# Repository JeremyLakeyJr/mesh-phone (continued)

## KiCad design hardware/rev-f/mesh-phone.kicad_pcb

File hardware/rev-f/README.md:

# Owasso1 Rev F — engineering checkpoint, not a fabrication release

Open `mesh-phone.kicad_pro` in this directory. The project in `../main/` is
the preserved original, not this corrected revision.

Implemented in schematic and PCB:

- MAX-M10S GPS with passive-antenna U.FL, UART, PPS and bypass capacitors.
- Rear keyed 10-pin JST-GH expansion interface, with a current-limited 3.3 V
  supply and shared SPI/I²C. Switch off and disconnect USB before swapping.
- MCU EN/BOOT support, usable SPI pin assignments, keypad expander pin-order
  corrections, display controls and I²C pull-ups.
- Removal of the switch connection that directly joined USB 5 V to the battery.
- Reconciled schematic/PCB pad contracts, with original component placements
  preserved. New parts are rear-mounted.

Read [INTERFACES.md](INTERFACES.md) before designing a module. This is a keyed
cable connector, not a finished blind-mate mechanical docking system.

## Not safe to order or power yet

The inherited battery protection, charger/power path, 3.3 V regulator and 5 V
boost circuits still require redesign. The A7670E modem/carrier is not approved
for the US target. Remaining radio-control, IR, fuel-gauge, RFID and SIM
interfaces are incomplete. See the full
[connection review](../../docs/reviews/review-2026-09-20/CONNECTION_REVIEW.md).

RF/USB impedance and antenna/enclosure placement are unverified. Ground vias
at the new reset circuitry overlap solderable pads; move them outside pads or
specify a suitable filled/capped via process during the final DFM pass. Do not
assume ordinary open vias in solder pads are assembly-ready.

## Verification evidence

Latest checkpoint: **608/608 contract and placement checks passed**. Native
KiCad DRC reports **0 errors, 0 unconnected items and 0 schematic-parity
findings**, with 5 footprint-library mismatch warnings. ERC still reports
**2 errors and 24 warnings** from unresolved supply modelling and interfaces.
The five footprint warnings concern J10, USB1, U1, J14 and J3; their modified
pad/geometry contracts need final library and manufacturer-drawing review.

- `verification-summary.json`: independent net/placement checks, native tool
  counts and SHA-256 fingerprints of the checked files.
- `drc-final.json`: native KiCad DRC, including schematic parity.
- `erc.json`: unresolved electrical-rule findings, not waived with power flags.
- `owasso1-engineering.pdf`: two-sheet schematic for review.
- `previews/`: schematic SVGs.

Zero routing errors would not certify circuit operation. Firmware, bench
bring-up, battery-safety verification, RF tests and cellular carrier acceptance
are still required. No revised manufacturing package has been released.

To repeat the read-only contract checks, run `python scripts/verify_revF.py` from the
repository root after exporting a fresh `netlist.xml`. The build/routing and
layout experiment scripts in `../../archive/scripts/` are checkpoint tools, not an
idempotent pipeline: do not replay them on this finished checkpoint.

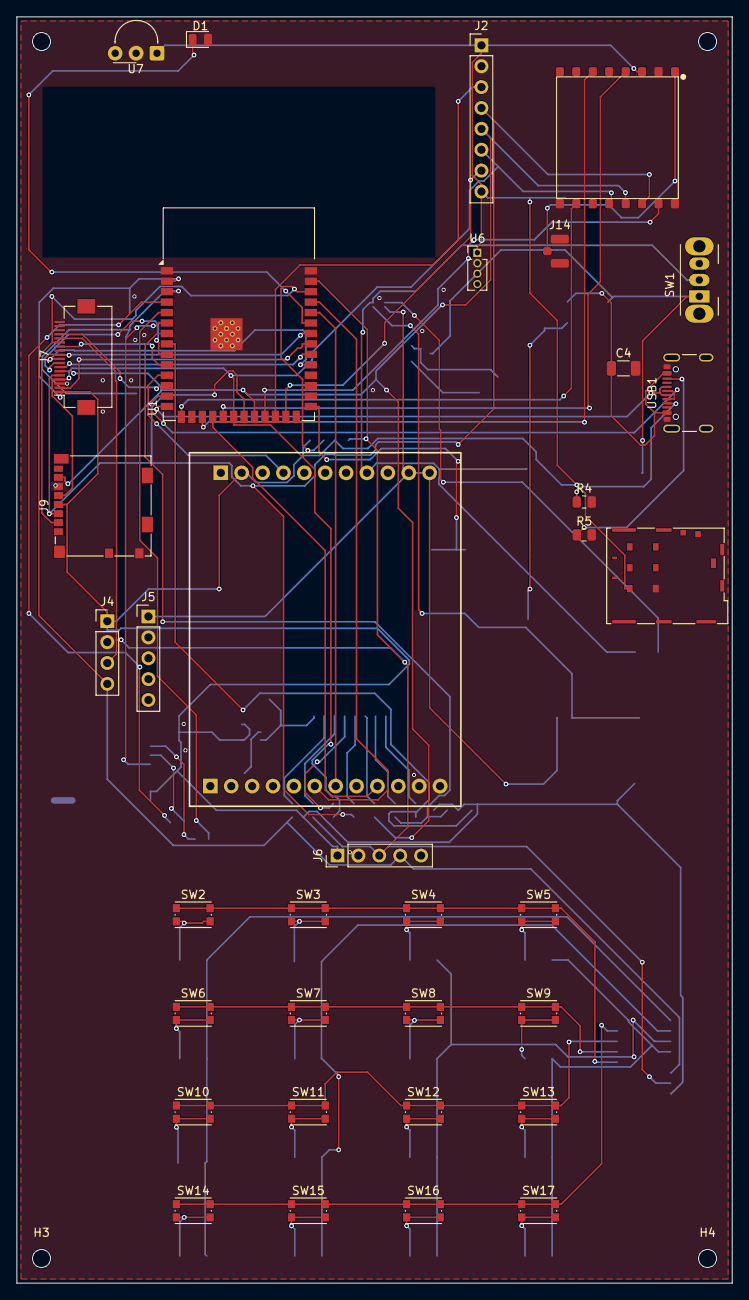
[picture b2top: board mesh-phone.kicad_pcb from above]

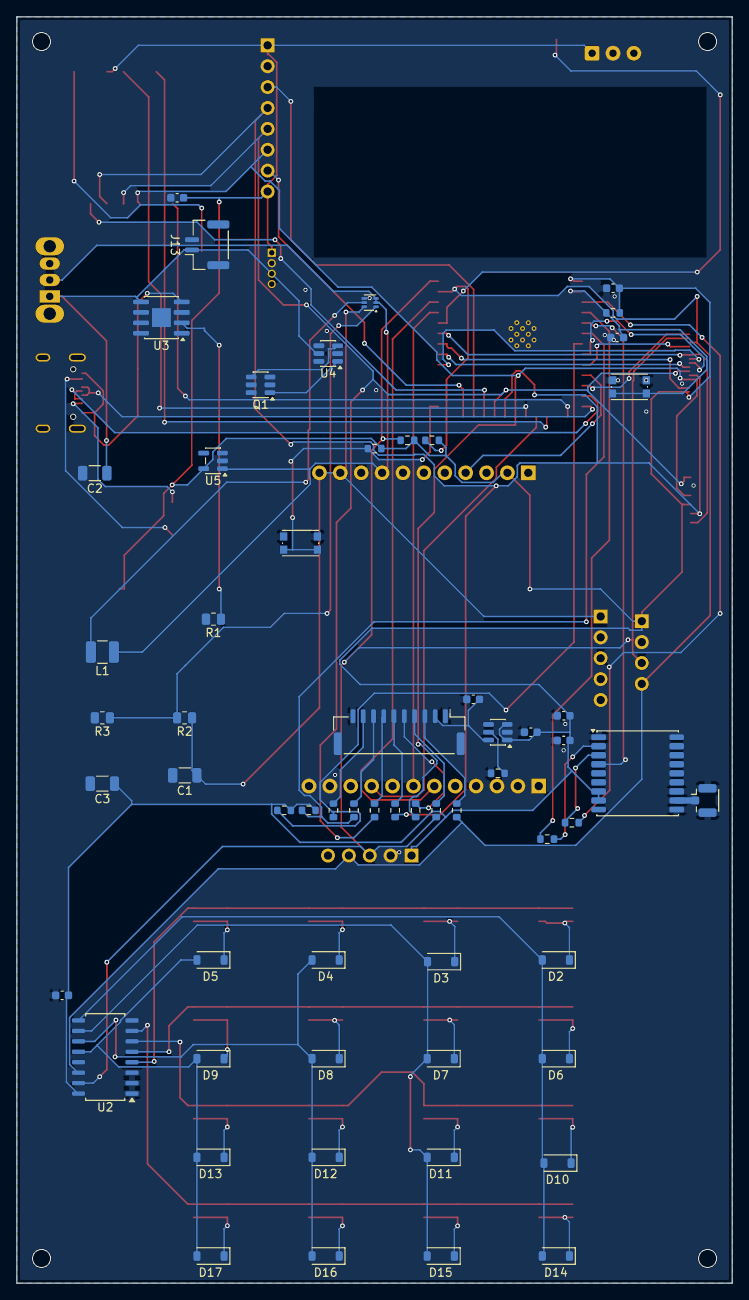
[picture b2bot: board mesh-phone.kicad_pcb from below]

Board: 2 copper layers, 87.0 x 154.0 mm, 99 parts (61 on the bottom side), 82 nets.

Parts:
C1: 1000uF-MODEM-BULK; C_1206_3216Metric
C2: 100uF-VBAT-BULK; C_1206_3216Metric
C3: 10uF-3V3-BULK; C_1206_3216Metric
C4: 10uF-USB-IN; C_1206_3216Metric
C5, C9: 10uF 10V X5R; C_0603_1608Metric
C6, C10, C11, C12: 100nF 10V X7R; C_0603_1608Metric
C7, C8: 1uF 10V X7R; C_0603_1608Metric
D1: TSAL6200-IR-LED; LED_0805_2012Metric
D2: 1N4148W-KEY-1; D_SOD-123
D3: 1N4148W-KEY-2; D_SOD-123
D4: 1N4148W-KEY-3; D_SOD-123
D5: 1N4148W-KEY-4; D_SOD-123
D6: 1N4148W-KEY-5; D_SOD-123
D7: 1N4148W-KEY-6; D_SOD-123
D8: 1N4148W-KEY-7; D_SOD-123
D9: 1N4148W-KEY-8; D_SOD-123
D10: 1N4148W-KEY-9; D_SOD-123
D11: 1N4148W-KEY-10; D_SOD-123
D12: 1N4148W-KEY-11; D_SOD-123
D13: 1N4148W-KEY-12; D_SOD-123
D14: 1N4148W-KEY-13; D_SOD-123
D15: 1N4148W-KEY-14; D_SOD-123
D16: 1N4148W-KEY-15; D_SOD-123
D17: 1N4148W-KEY-16; D_SOD-123
H1, H2, H3, H4: MountingHole_2.2mm_M2
J1: A7670E-LASE-23P-12+11; A7670E_LASE_23P_12+11
J2: CC1101-module; PinHeader_1x08_P2.54mm_Vertical
J3: Ra-01SH-SX1262-915MHz; Ra-01SH
J4: PN532-NFC-module; PinHeader_1x04_P2.54mm_Vertical
J5: RDM6300-RFID-module; PinHeader_1x05_P2.54mm_Vertical
J6: Pimoroni-PIM447-Trackball; PinHeader_1x05_P2.54mm_Vertical
J7: Waveshare-3.5in-18pin-FPC; Hirose_FH12-18S-0.5SH_1x18-1MP_P0.50mm_Horizontal
J9: MicroSD-SPI; microSD_HC_Molex_104031-0811
J10: Nano-SIM; JAE_SIM_Card_SF72S006
J13: LiPo-BATTERY-MICRO-JST-1.25; JST_GH_SM02B-GHS-TB_1x02-1MP_P1.25mm_Horizontal
J14: LoRa-UFL-Antenna; U.FL_Hirose_U.FL-R-SMT-1_Vertical
J15: GPS PASSIVE ANTENNA; U.FL_Hirose_U.FL-R-SMT-1_Vertical
J16: REAR EXPANSION - POWER OFF TO SWAP; JST_GH_BM10B-GHS-TBT_1x10-1MP_P1.25mm_Vertical
L1: 1uH-BOOST-INDUCTOR; L_1210_3225Metric
Q1: FS8205A-PROTECTION-FET; SOT-23-6
R1: 1.2k-TP4056-PROG; R_0805_2012Metric
R2: 180k-BOOST-FB; R_0805_2012Metric
R3: 27k-BOOST-FB; R_0805_2012Metric
R4: 5.1k-USB-C-CC1-Rd; R_0805_2012Metric
R5: 5.1k-USB-C-CC2-Rd; R_0805_2012Metric
R6, R7: 1k; R_0603_1608Metric
R8, R9, R12, R13: 10k; R_0603_1608Metric
R10, R11: 4.7k; R_0603_1608Metric
R14: 232k 1%; R_0603_1608Metric
R15, R16, R17, R18, R19, R20, R21: 33; R_0603_1608Metric
SW1: Power-switch; SW_Slide_SPDT_Angled_CK_OS102011MA1Q
SW2: KEY-1; SW_Push_1P1T_NO_CK_KMR2
SW3: KEY-2; SW_Push_1P1T_NO_CK_KMR2
SW4: KEY-3; SW_Push_1P1T_NO_CK_KMR2
SW5: KEY-4; SW_Push_1P1T_NO_CK_KMR2
SW6: KEY-5; SW_Push_1P1T_NO_CK_KMR2
SW7: KEY-6; SW_Push_1P1T_NO_CK_KMR2
SW8: KEY-7; SW_Push_1P1T_NO_CK_KMR2
SW9: KEY-8; SW_Push_1P1T_NO_CK_KMR2
SW10: KEY-9; SW_Push_1P1T_NO_CK_KMR2
SW11: KEY-10; SW_Push_1P1T_NO_CK_KMR2
SW12: KEY-11; SW_Push_1P1T_NO_CK_KMR2
SW13: KEY-12; SW_Push_1P1T_NO_CK_KMR2
SW14: KEY-13; SW_Push_1P1T_NO_CK_KMR2
SW15: KEY-14; SW_Push_1P1T_NO_CK_KMR2
SW16: KEY-15; SW_Push_1P1T_NO_CK_KMR2
SW17: KEY-16; SW_Push_1P1T_NO_CK_KMR2
SW18: BOOT; SW_Push_1P1T_NO_CK_KMR2
SW19: RESET; SW_Push_1P1T_NO_CK_KMR2
U1: ESP32-S3-WROOM-1-N16R8; ESP32-S3-WROOM-1
U2: PCF8574T-keypad-expander; SOIC-16_4.55x10.3mm_P1.27mm
U3: TP4056-charger; HSOP-8-1EP_3.9x4.9mm_P1.27mm_EP2.3x2.3mm
U4: DW01A-protection; SOT-23-6
U5: 3V3-LDO; SOT-23-5
U6: MAX17048-fuel-gauge; PinHeader_1x04_P1.27mm_Vertical
U7: TSOP38238-IR-receiver; Vishay_MINIMOLD-3Pin
U8: TPS61023DRLR-5V-BOOST; SOT-563
U9: MAX-M10S-00B-01; ublox_MAX
U10: TPS2553DBVR; SOT-23-6
USB1: USB-C-charge-and-data; USB_C_Receptacle_GCT_USB4105-xx-A_16P_TopMnt_Horizontal

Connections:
/3V3: C3.1, C5.1, C6.1, C8.1, C10.1, C11.1, C12.1, J1.14, J2.1, J2.8, J3.3, J4.1, J6.1, J7.1, J9.4, J10.1, R8.1, R9.1, R10.1, R11.1, R12.1, R13.1, U1.2, U2.16, U5.5, U6.1, U7.1, U9.7, U9.8, U10.1, U10.3
/BAT_CHARGE: C2.1, J13.1, SW1.1, U3.5, U4.5, U6.3
/BOOST_FB: R2.2, R3.1, U8.1
/BOOST_SW: L1.2, U8.5
/CC1101_CS: J2.3, U1.24
/CC1101_GDO0: J2.7, U1.25
/DW01A_OC: Q1.4, U4.3
/DW01A_OD: Q1.1, U4.1
/EXP_CS: R12.2, R20.1, U1.7
/EXP_IRQ: R13.2, R21.1, U1.8
/GND: C1.2, C2.2, C3.2, C4.2, C5.2, C6.2, C7.2, C8.2, C9.2, C10.2, C11.2, C12.2, D1.2, J1.11, J1.12, J2.2, J3.2, J3.9, J3.16, J4.2, J5.2, J6.2, J7.3, J9.6, J9.10, J10.2, J13.2, J14.2, J15.2, J16.1, J16.10, Q1.2, Q1.3, Q1.5, Q1.6, R1.2, R3.2, R4.2, R5.2, R14.2, SW18.2, SW19.2, U1.1, U1.40, U1.41, U2.1, U2.2, U2.3, U2.8, U3.3, U3.9, U4.2, U4.4, U4.6, U5.2, U6.2, U7.2, U8.4, U9.1, U9.10, U9.12, U10.2, USB1.1, USB1.12, USB1.13, USB1.22
/GPS and rear expansion/EXP_3V3: C9.1, J16.2, U10.6
/GPS and rear expansion/EXP_CS_PORT: J16.8, R20.2
/GPS and rear expansion/EXP_ILIM: R14.1, U10.5
/GPS and rear expansion/EXP_IRQ_PORT: J16.9, R21.2
/GPS and rear expansion/EXP_MISO: J16.7, R19.2
/GPS and rear expansion/EXP_MOSI: J16.6, R18.2
/GPS and rear expansion/EXP_SCK: J16.5, R17.2
/GPS and rear expansion/EXP_SCL: J16.3, R15.2
/GPS and rear expansion/EXP_SDA: J16.4, R16.2
/GPS and rear expansion/GPS_ANT: J15.1, U9.11
/GPS and rear expansion/GPS_RX: R6.2, U9.3
/GPS and rear expansion/GPS_TX: R7.1, U9.2
/GPS_HOST_RX: R7.2, U1.5
/GPS_HOST_TX: R6.1, U1.4
/GPS_PPS: U1.6, U9.4
/I2C_SCL: J4.4, J6.4, J7.13, R10.2, R15.1, U1.38, U2.14
/I2C_SDA: J4.3, J6.3, J7.14, R11.2, R16.1, U1.39, U2.15
/IR_TX: D1.1, U1.35
/KEY_C1: D2.2, D6.2, D10.2, D14.2, U2.9
/KEY_C2: D3.2, D7.2, D11.2, D15.2, U2.10
/KEY_C3: D4.2, D8.2, D12.2, D16.2, U2.11
/KEY_C4: D5.2, D9.2, D13.2, D17.2, U2.12
/KEY_D1: D2.1, SW2.2
/KEY_D2: D3.1, SW3.2
/KEY_D3: D4.1, SW4.2
/KEY_D4: D5.1, SW5.2
/KEY_D5: D6.1, SW6.2
/KEY_D6: D7.1, SW7.2
/KEY_D7: D8.1, SW8.2
/KEY_D8: D9.1, SW9.2
/KEY_D9: D10.1, SW10.2
/KEY_D10: D11.1, SW11.2
/KEY_D11: D12.1, SW12.2
/KEY_D12: D13.1, SW13.2
/KEY_D13: D14.1, SW14.2
/KEY_D14: D15.1, SW15.2
/KEY_D15: D16.1, SW16.2
/KEY_D16: D17.1, SW17.2
/KEY_R1: SW2.1, SW3.1, SW4.1, SW5.1, U2.4
/KEY_R2: SW6.1, SW7.1, SW8.1, SW9.1, U2.5
/KEY_R3: SW10.1, SW11.1, SW12.1, SW13.1, U2.6
/KEY_R4: SW14.1, SW15.1, SW16.1, SW17.1, U2.7
/LCD_BL: J7.2, U1.33
/LCD_CS: J7.9, U1.31
/LCD_DC: J7.7, U1.32
/LCD_RESET: J7.8, U1.9
/LORA_ANT: J3.1, J14.1
/LTE_PWRKEY: J1.9, U1.18
/LTE_RI: J1.16, U1.11
/LTE_RX: J1.7, U1.36
/LTE_TX: J1.6, U1.37
/MCU_BOOT: R9.2, SW18.1, U1.27
/MCU_EN: C7.1, R8.2, SW19.1, U1.3
/MODEM_5V: C1.1, J1.22, J1.23, J5.1, R2.1, U8.6
/SD_CS: J7.10, J9.2, U1.34
/SPI_MISO: J2.5, J3.13, J7.6, J9.7, R19.1, U1.22
/SPI_MOSI: J2.4, J3.14, J7.5, J9.3, R18.1, U1.21
/SPI_SCK: J2.6, J3.12, J7.4, J9.5, R17.1, U1.20
/SX1262_BUSY: J3.10, U1.15
/SX1262_CS: J3.15, U1.23
/SX1262_DIO1: J3.6, U1.17
/SX1262_RESET: J3.4, U1.19
/TOUCH_INT: J7.15, U1.12
/TP_RESET: J7.12, U1.10
/U3_PROG: R1.1, U3.2
/USB_CC1: R4.1, USB1.5
/USB_CC2: R5.1, USB1.15
/USB_D+: U1.14, USB1.6, USB1.16
/USB_D-: U1.13, USB1.7, USB1.17
/VBAT: J1.20, L1.1, SW1.2, U5.1, U8.2, U8.3
/VBUS5V: C4.1, U3.4, USB1.4, USB1.9, USB1.14, USB1.19

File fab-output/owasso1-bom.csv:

"Refs","Value","Footprint","Qty","DNP"
"C1","1000uF-MODEM-BULK","Capacitor_SMD:C_1206_3216Metric","1",""
"C2","100uF-VBAT-BULK","Capacitor_SMD:C_1206_3216Metric","1",""
"C3","10uF-3V3-BULK","Capacitor_SMD:C_1206_3216Metric","1",""
"C4","10uF-USB-IN","Capacitor_SMD:C_1206_3216Metric","1",""
"D1","TSAL6200-IR-LED","LED_SMD:LED_0805_2012Metric","1",""
"D2","1N4148W-KEY-1","Diode_SMD:D_SOD-123","1",""
"D3","1N4148W-KEY-2","Diode_SMD:D_SOD-123","1",""
"D4","1N4148W-KEY-3","Diode_SMD:D_SOD-123","1",""
"D5","1N4148W-KEY-4","Diode_SMD:D_SOD-123","1",""
"D6","1N4148W-KEY-5","Diode_SMD:D_SOD-123","1",""
"D7","1N4148W-KEY-6","Diode_SMD:D_SOD-123","1",""
"D8","1N4148W-KEY-7","Diode_SMD:D_SOD-123","1",""
"D9","1N4148W-KEY-8","Diode_SMD:D_SOD-123","1",""
"D10","1N4148W-KEY-9","Diode_SMD:D_SOD-123","1",""
"D11","1N4148W-KEY-10","Diode_SMD:D_SOD-123","1",""
"D12","1N4148W-KEY-11","Diode_SMD:D_SOD-123","1",""
"D13","1N4148W-KEY-12","Diode_SMD:D_SOD-123","1",""
"D14","1N4148W-KEY-13","Diode_SMD:D_SOD-123","1",""
"D15","1N4148W-KEY-14","Diode_SMD:D_SOD-123","1",""
"D16","1N4148W-KEY-15","Diode_SMD:D_SOD-123","1",""
"D17","1N4148W-KEY-16","Diode_SMD:D_SOD-123","1",""
"J1","A7670E-LASE-23P-12+11","owasso1:A7670E_LASE_23P_12+11","1",""
"J2","CC1101-module","Connector_PinHeader_2.54mm:PinHeader_1x08_P2.54mm_Vertical","1",""
"J3","Ra-01SH-SX1262-915MHz","owasso1:Ra-01SH","1",""
"J4","PN532-NFC-module","Connector_PinHeader_2.54mm:PinHeader_1x04_P2.54mm_Vertical","1",""
"J5","RDM6300-RFID-module","Connector_PinHeader_2.54mm:PinHeader_1x05_P2.54mm_Vertical","1",""
"J6","Pimoroni-PIM447-Trackball","Connector_PinHeader_2.54mm:PinHeader_1x05_P2.54mm_Vertical","1",""
"J7","Waveshare-3.5in-18pin-FPC","Connector_FFC-FPC:Hirose_FH12-18S-0.5SH_1x18-1MP_P0.50mm_Horizontal","1",""
"J9","MicroSD-SPI","Connector_PinHeader_2.54mm:PinHeader_1x10_P2.54mm_Vertical","1",""
"J10","Nano-SIM","Connector_PinHeader_2.54mm:PinHeader_1x06_P2.54mm_Vertical","1",""
"J13","LiPo-BATTERY-MICRO-JST-1.25","Connector_JST:JST_GH_SM02B-GHS-TB_1x02-1MP_P1.25mm_Horizontal","1",""
"J14","LoRa-UFL-Antenna","owasso1:U.FL_Hirose_U.FL-R-SMT-1_Vertical","1",""
"L1","1uH-BOOST-INDUCTOR","Inductor_SMD:L_1210_3225Metric","1",""
"Q1","FS8205A-PROTECTION-FET","Package_TO_SOT_SMD:SOT-23-6","1",""
"R1","1.2k-TP4056-PROG","Resistor_SMD:R_0805_2012Metric","1",""
"R2","180k-BOOST-FB","Resistor_SMD:R_0805_2012Metric","1",""
"R3","27k-BOOST-FB","Resistor_SMD:R_0805_2012Metric","1",""
"R4","5.1k-USB-C-CC1-Rd","Resistor_SMD:R_0805_2012Metric","1",""
"R5","5.1k-USB-C-CC2-Rd","Resistor_SMD:R_0805_2012Metric","1",""
"SW1","Power-switch","Button_Switch_SMD:SW_SPDT_CK_JS102011SAQN","1",""
"SW2","KEY-1","Button_Switch_SMD:SW_SPST_B3S-1000","1",""
"SW3","KEY-2","Button_Switch_SMD:SW_SPST_B3S-1000","1",""
"SW4","KEY-3","Button_Switch_SMD:SW_SPST_B3S-1000","1",""
"SW5","KEY-4","Button_Switch_SMD:SW_SPST_B3S-1000","1",""
"SW6","KEY-5","Button_Switch_SMD:SW_SPST_B3S-1000","1",""
"SW7","KEY-6","Button_Switch_SMD:SW_SPST_B3S-1000","1",""
"SW8","KEY-7","Button_Switch_SMD:SW_SPST_B3S-1000","1",""
"SW9","KEY-8","Button_Switch_SMD:SW_SPST_B3S-1000","1",""
"SW10","KEY-9","Button_Switch_SMD:SW_SPST_B3S-1000","1",""
"SW11","KEY-10","Button_Switch_SMD:SW_SPST_B3S-1000","1",""
"SW12","KEY-11","Button_Switch_SMD:SW_SPST_B3S-1000","1",""
"SW13","KEY-12","Button_Switch_SMD:SW_SPST_B3S-1000","1",""
"SW14","KEY-13","Button_Switch_SMD:SW_SPST_B3S-1000","1",""
"SW15","KEY-14","Button_Switch_SMD:SW_SPST_B3S-1000","1",""
"SW16","KEY-15","Button_Switch_SMD:SW_SPST_B3S-1000","1",""
"SW17","KEY-16","Button_Switch_SMD:SW_SPST_B3S-1000","1",""
"U1","ESP32-S3-WROOM-1-N16R8","RF_Module:ESP32-S3-WROOM-1","1",""
"U2","PCF8574T-keypad-expander","Package_SO:SOIC-16_3.9x9.9mm_P1.27mm","1",""
"U3","TP4056-charger","Package_SO:HSOP-8-1EP_3.9x4.9mm_P1.27mm_EP2.3x2.3mm","1",""
"U4","DW01A-protection","Package_TO_SOT_SMD:SOT-23-6","1",""
"U5","3V3-LDO","Package_TO_SOT_SMD:SOT-23-5","1",""
"U6","MAX17048-fuel-gauge","Connector_PinHeader_2.54mm:PinHeader_1x04_P2.54mm_Vertical","1",""
"U7","TSOP38238-IR-receiver","Connector_PinHeader_2.54mm:PinHeader_1x03_P2.54mm_Vertical","1",""
"U8","TPS61023DRLR-5V-BOOST","Package_TO_SOT_SMD:SOT-563","1",""
"USB1","USB-C-charge-and-data","Connector_USB:USB_C_Receptacle_GCT_USB4105-xx-A_16P_TopMnt_Horizontal","1",""

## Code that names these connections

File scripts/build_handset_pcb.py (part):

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    add(ref,value,f'Connector_Generic:Conn_01x{count:02}',dict(enumerate(nets,1)),x,y,side,angle,sheet,fp)

# Existing N16R8 module stays. GPIO35/36/37 are occupied by octal PSRAM.
gpio = {4:'GPS_HOST_TX',5:'GPS_HOST_RX',6:'GPS_PPS',7:'EXP_CS',15:'EXP_IRQ',
        16:'SX_RESET',17:'SX_BUSY',18:'SX_DIO1',8:'KEY_IRQ',9:'I2C_SCL',10:'I2C_SDA',
        11:'LCD_CS',12:'SPI_SCK',13:'SPI_MOSI',14:'SPI_MISO',21:'SX_CS',47:'CC_CS',48:'CC_GDO0',
        38:'I2S_BCLK',39:'I2S_LRCLK',40:'I2S_DOUT',41:'I2S_DIN',42:'IR_TX',2:'SD_CS',1:'NFC_CS'}
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    keynets[8-i] = 'KEY_ROW'+str(i)
    keynets[9+i] = 'KEY_COL'+str(i)
# Spare scanner GPIO supplies slow controls; timing-sensitive inputs stay on ESP32.
for pin,net in {1:'LCD_DC',2:'LCD_RESET',3:'TOUCH_RESET',4:'MEDIA_EN',13:'LTE_ON',14:'IR_RX',15:'TOUCH_IRQ',16:'NFC_IRQ',17:'RFID_DIN',18:'RFID_CLK'}.items():
    keynets[pin]=net
add('U2','TCA8418RTWR','Handset:TCA8418',keynets,123,119,side='F',sheet='keys')
passive('C4','100nF',['+3V3','GND'],128,119,sheet='keys',side='F')
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
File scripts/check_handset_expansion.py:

#!/usr/bin/env python3
"""Check expansion circuit and native copper independently of routing manifests."""
import json,sys
from pathlib import Path
import xml.etree.ElementTree as ET
import pcbnew as p
from handset_expansion_contract import PINS,validate
p.SwigPyIterator.next=p.SwigPyIterator.__next__
ROOT=Path(__file__).resolve().parents[1]/'hardware/handset-rev-a/generated'
GROUPS={
 '+3V3':'U7.6 U14.1 C40.1 R42.1 U33.10 U34.20 U35.14 C91.1 C92.1 C93.1 R86.1 R1.1 R3.1 R4.1',
 'EXP_3V3':'U14.6 C41.1 R87.1 J16.2',
 'EXP_PWR_EN':'U33.1 U35.1 R83.1 U14.3',
 'EXP_IO_ARM':'U33.3 U35.2 R84.1',
 'EXP_FAULT_N':'U14.4 R42.2 U33.2 U35.13',
 'EXP_IO_OE_N':'U35.12 U34.19 R86.2',
 'EXP_ILIM':'U14.5 R41.1','EXP_GPIO_SPARE':'U33.4 R85.1',
 'MCU_EN':'U1.3 U33.6 R1.2 C1.1',
 'I2C_SCL':'U1.17 U33.8 U34.2 R3.2','I2C_SDA':'U1.18 U33.9 U34.3 R4.2',
 'SPI_SCK':'U1.20 U34.4','SPI_MOSI':'U1.21 U34.5','SPI_MISO':'U1.22 U34.6',
 'EXP_CS':'U1.7 U34.7','EXP_IRQ':'U1.8 U34.8',
 'GND':'U7.8 U14.2 R41.2 C40.2 C41.2 U33.5 U34.9 U34.10 U34.11 U35.3 U35.4 U35.5 U35.7 U35.9 U35.10 U35.11 C91.2 C92.2 C93.2 R83.2 R84.2 R85.2 R87.2 J16.1 J16.10 U15.3 U15.8 U16.3 U16.8 C1.2',
}
for ref,channel,pin in [('R20','SCL',18),('R21','SDA',17),('R22','SCK',16),('R23','MOSI',15),('R24','MISO',14),('R25','CS',13),('R26','IRQ',12)]:GROUPS['EXP_SW_'+channel]=f'U34.{pin} {ref}.1'
for net,ref,jpin,esd in [('EXP_SCL','R20',3,'U15.1'),('EXP_SDA','R21',4,'U15.2'),('EXP_SCK','R22',5,'U15.4'),('EXP_MOSI','R23',6,'U15.5'),('EXP_MISO','R24',7,'U16.1'),('EXP_CS_PORT','R25',8,'U16.2'),('EXP_IRQ_PORT','R26',9,'U16.4')]:GROUPS[net]=f'{ref}.2 J16.{jpin} {esd}'

def check_board(board):
 board.BuildConnectivity();pads={f.GetReference()+'.'+q.GetNumber():q for f in board.GetFootprints() for q in f.Pads() if q.GetNumber()}
 contract=[]
 for ref,pins in PINS.items():
  for pin,net in pins.items():
   q=pads.get(ref+'.'+pin)
   if not q or (q.GetNetname()!=net if net is not None else not q.GetNetname().startswith('unconnected-(')):contract.append(ref+'.'+pin)
 checks=[]
 for net,names in GROUPS.items():
  names=names.split();seed=pads.get(names[0]);connected=list(board.GetConnectivity().GetConnectedItems(seed)) if seed else []
  ids={q.m_Uuid.AsString() for q in connected}|({seed.m_Uuid.AsString()} if seed else set())
  missing=[n for n in names if n not in pads or pads[n].m_Uuid.AsString() not in ids]
  wrong=[n for n in names if n not in pads or pads[n].GetNetname()!=net]
  unexpected=sorted({q.GetNetname() for q in connected if q.GetNetname()!=net})
  checks.append(dict(net=net,pads=names,disconnected=missing,wrong_net=wrong,unexpected_nets=unexpected,passed=not(missing or wrong or unexpected)))
 return dict(passed=not contract and all(g['passed'] for g in checks),groups=checks,pin_contract_failures=contract,fabrication_released=False,scope='Connectivity and topology only; not startup, isolation leakage, current, thermal, fault recovery or signal-timing qualification')

def check_circuit(out):
 spec={c['ref']:c for c in json.loads((out/'connectivity.json').read_text())};xml=ET.parse(out/'netlist.xml').getroot()
 values={c.attrib['ref']:c.findtext('value') for c in xml.findall('./components/comp')}
 nets={(n.attrib['ref'],n.attrib['pin']):net.attrib['name'] for net in xml.findall('./nets/net') for n in net.findall('node')}
 fields={c.attrib['ref']:{f.attrib['name']:f.text for f in c.findall('./fields/field')} for c in xml.findall('./components/comp')}
 validate(spec,values,nets,fields)
 return spec,values,nets,fields
if __name__=='__main__':
 out=Path(sys.argv[1]) if len(sys.argv)>1 else ROOT;check_circuit(out)
 report=check_board(p.LoadBoard(str(out/'handset.kicad_pcb')))
 (out/'expansion-routing-check.json').write_text(json.dumps(report,indent=2)+'\n');print(json.dumps(report,indent=2));sys.exit(0 if report['passed'] else 1)

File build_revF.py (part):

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    changes.append({'ref':ref, 'pin':str(number), 'net':net})

# Free general-purpose GPIOs. GPIO35/36/37 are occupied by octal PSRAM.
for pin, net in {3:'MCU_EN',4:'GPS_HOST_TX',5:'GPS_HOST_RX',6:'GPS_PPS',
                 7:'EXP_CS',8:'EXP_IRQ',9:'LCD_RESET',10:'TP_RESET',12:'TOUCH_INT',
                 16:None,20:'SPI_SCK',21:'SPI_MOSI',22:'SPI_MISO',
                 23:'SX1262_CS',24:'CC1101_CS',25:'CC1101_GDO0',26:None,
                 27:'MCU_BOOT',28:None,29:None,30:None}.items():
    set_pin('U1', pin, net)
# Correct SO16 address pins and P0-P7. Pin 13 remains optional polling IRQ.
for pin, net in {1:'GND',2:'GND',3:'GND',4:'KEY_R1',5:'KEY_R2',6:'KEY_R3',
                 7:'KEY_R4',9:'KEY_C1',10:'KEY_C2',11:'KEY_C3',12:'KEY_C4'}.items():
    set_pin('U2', pin, net)
# Separate protected pack/charger rail from switched system rail. In particular,
# never connect USB VBUS directly to a cell through the slide switch.
for ref, pin in [('J13',1),('U3',5),('C2',1),('U4',5),('U6',3),('SW1',1)]:
    set_pin(ref, pin, 'BAT_CHARGE')

# Correct the three legacy connector-shaped symbols to their actual pad sets.
# Keep existing pin coordinates so this does not disturb other schematic wiring.
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
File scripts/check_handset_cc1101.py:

#!/usr/bin/env python3
"""Check the CC1101 manufacturer-derived circuit, not RF performance.

The expected graph is independent of the generator and rejects missing,
shorted or swapped matching branches. Uses the native exported KiCad netlist.
"""
from collections import Counter
import copy
import json
from pathlib import Path
import sys
import xml.etree.ElementTree as ET

ROOT=Path(__file__).resolve().parents[1]

# TI SWRS061I Fig11 / SWRR045 rev3.0, with optional C126/L125 omitted.
# Each unordered pair is the two terminals of one passive component.
RF={
 'L5':('CC_RF_P','CC_BAL_P','12nH 5%'),       # L121
 'L6':('CC_RF_N','CC_BAL_N','12nH 5%'),       # L131
 'L7':('CC_BAL_P','CC_SHUNT','18nH 5%'),      # L122
 'L8':('CC_BAL_N','CC_MATCH','18nH 5%'),      # L132
 'L9':('CC_MATCH','CC_LPF','12nH 5%'),        # L123
 'L10':('CC_LPF','CC_DC_BLOCK','12nH 5%'),    # L124
 'C63':('CC_BAL_P','CC_BAL_N','1pF 0.25pF C0G 50V'),
 'C64':('CC_BAL_P','CC_MATCH','1.5pF 0.25pF C0G 50V'),
 'C65':('CC_LPF','GND','3.3pF 0.25pF C0G 50V'),
 'C66':('CC_SHUNT','GND','100pF 5% C0G 50V'),
 'C67':('CC_DC_BLOCK','CC_RF_50R','12pF 5% C0G 50V'),
 'C68':('CC_BAL_N','GND','1.5pF 0.25pF C0G 50V'),
}


def checks(nets, values, mpns):
    result=[]
    def check(name,valid):result.append(dict(check=name,passed=bool(valid)))
    for ref,(a,b,value) in RF.items():
        check(ref+' TI matching branch',Counter(nets.get((ref,p)) for p in ('1','2'))==Counter((a,b)))
        check(ref+' TI matching value',values.get(ref)==value)
    for pin,net in {'1':'SPI_SCK','2':'SPI_MISO','3':'CC_GDO2','4':'CC_VDD',
      '5':'CC_DCOUPL','6':'CC_GDO0','7':'CC_CS','8':'CC_X1','9':'CC_VDD',
      '10':'CC_X2','11':'CC_VDD','12':'CC_RF_P','13':'CC_RF_N','14':'CC_VDD',
      '15':'CC_VDD','16':'GND','17':'CC_RBIAS','18':'CC_VDD','19':'GND',
      '20':'SPI_MOSI','21':'GND'}.items():check('U5.'+pin+' contract',nets.get(('U5',pin))==net)
    for key,net in {('Y2','1'):'CC_X1',('Y2','2'):'GND',('Y2','3'):'CC_X2',('Y2','4'):'GND',
                   ('C61','1'):'CC_X1',('C61','2'):'GND',('C62','1'):'CC_X2',('C62','2'):'GND',
                   ('C11','1'):'CC_DCOUPL',('C11','2'):'GND',('L11','1'):'+3V3',('L11','2'):'CC_VDD',
                   ('R11','1'):'CC_RBIAS',('R11','2'):'GND',('R12','1'):'+3V3',('R12','2'):'CC_CS',
                   ('J21','1'):'CC_RF_50R',('J21','2'):'GND',('TP1','1'):'CC_GDO2'}.items():
        check('.'.join(key)+' contract',nets.get(key)==net)
    for ref in ['C12','C69','C70','C71','C72','C73','C74']:
        check(ref+' bypass rail',nets.get((ref,'1'))=='CC_VDD' and nets.get((ref,'2'))=='GND')
        check(ref+' bypass value',values.get(ref)==('1uF 10% X5R 10V' if ref=='C74' else '100nF 10% X7R 16V'))
    for ref in ('C61','C62'):check(ref+' CL10 load',values.get(ref)=='15pF 5% C0G 50V')
    check('26MHz specified crystal',mpns.get('Y2')=='ABM8-26.000MHZ-10-D-1-G-T')
    check('bias resistor',values.get('R11')=='56k 1%')
    check('crystal load estimate',15/2+2.5==10)
    check('first-year crystal error budget',10+15+2<40)
    # Exact node membership catches unintended bypasses or extra grounded legs.
    expected={}
    for ref,(a,b,_) in RF.items():
        expected.setdefault(a,set()).add(ref);expected.setdefault(b,set()).add(ref)
    for net in ('CC_BAL_P','CC_BAL_N','CC_SHUNT','CC_MATCH','CC_LPF','CC_DC_BLOCK'):
        check(net+' branch membership',{ref for (ref,pin),n in nets.items() if n==net}==expected[net])
    return result


def inspect(path):
    xml=ET.parse(path/'netlist.xml').getroot()
    nets={(n.get('ref'),n.get('pin')):net.get('name') for net in xml.findall('./nets/net') for n in net.findall('node')}
    comps={c.get('ref'):c for c in xml.findall('./components/comp')}
    values={ref:c.findtext('value') for ref,c in comps.items()}
    mpns={ref:c.findtext('fields/field[@name="MPN"]') for ref,c in comps.items()}
    results=checks(nets,values,mpns)
    negative=[]
    for key,new in [(('C63','2'),'GND'),(('L8','2'),'CC_BAL_P'),(('Y2','2'),'CC_X1'),(('C11','1'),'CC_VDD')]:
        changed=copy.deepcopy(nets);changed[key]=new
        negative.append(dict(mutation='.'.join(key)+' -> '+new,rejected=not all(x['passed'] for x in checks(changed,values,mpns))))
    wrong=copy.deepcopy(values);wrong['C61']='27pF'
    negative.append(dict(mutation='C61 wrong crystal load',rejected=not all(x['passed'] for x in checks(nets,wrong,mpns))))
    return dict(scope='CC1101 schematic topology and component specification; not copper continuity or RF qualification',
        passed=all(x['passed'] for x in results) and all(x['rejected'] for x in negative),
        checks=len(results),failures=[x for x in results if not x['passed']],negative_tests=negative,
        fabrication_released=False)


if __name__=='__main__':
    path=Path(sys.argv[1]) if len(sys.argv)>1 else ROOT/'hardware/handset-rev-a/generated'
    result=inspect(path);(path/'cc1101-checks.json').write_text(json.dumps(result,indent=2)+'\n')
    print(json.dumps(result,indent=2));sys.exit(0 if result['passed'] else 1)
